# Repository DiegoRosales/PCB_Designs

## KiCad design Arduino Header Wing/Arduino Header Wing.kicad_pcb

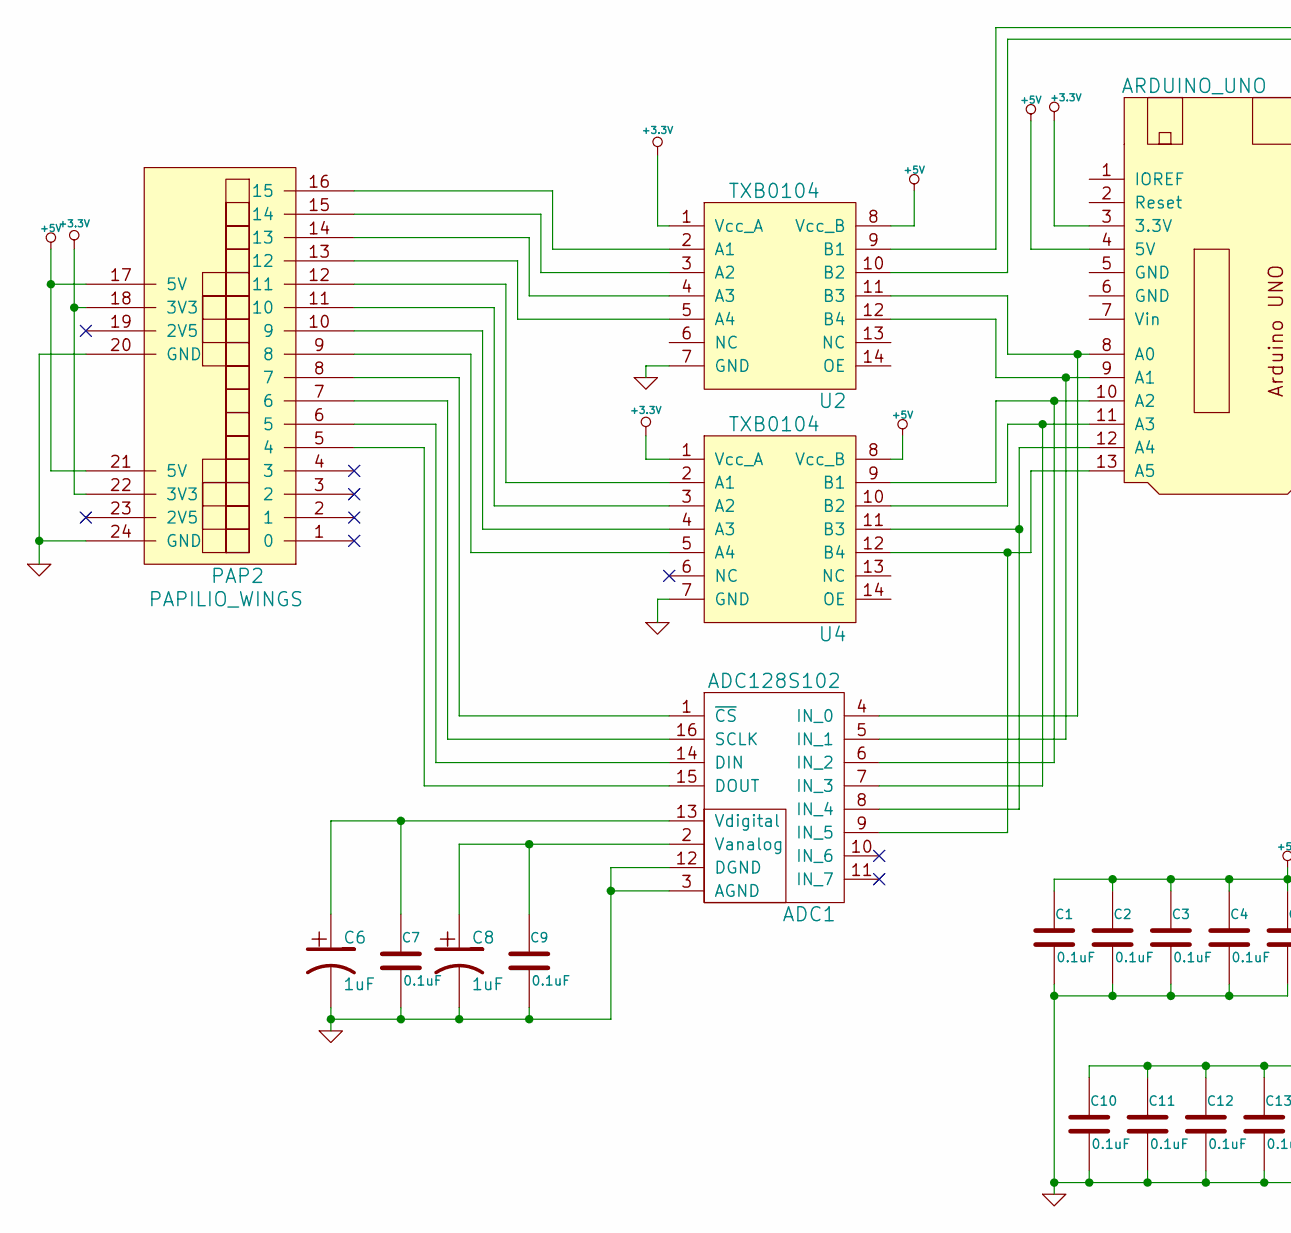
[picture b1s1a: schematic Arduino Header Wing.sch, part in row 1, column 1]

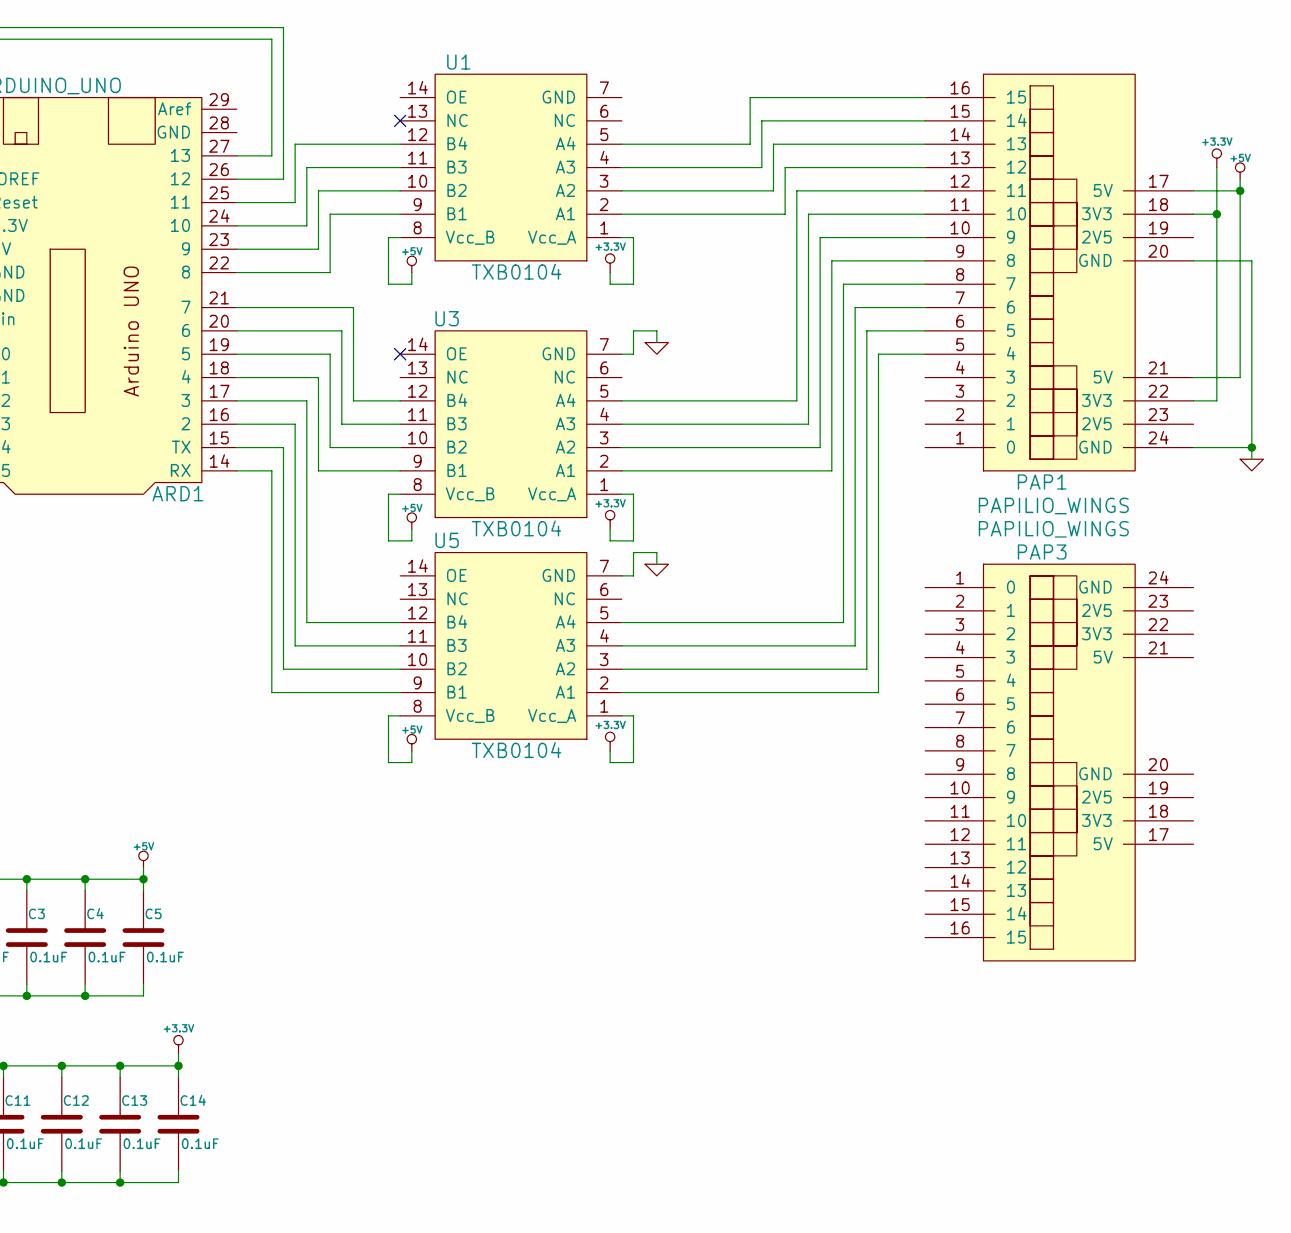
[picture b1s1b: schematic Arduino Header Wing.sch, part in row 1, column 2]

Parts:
ADC1: ADC128S102
ARD1: ARDUINO_UNO
C1, C2, C3, C4, C5, C7, C9, C10, C11, C12, C13, C14: 0.1uF
C6, C8: 1uF
PAP1, PAP2, PAP3: PAPILIO_WINGS
U1, U2, U3, U4, U5: TXB0104

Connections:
+3.3V: ARD1.3 (3.3V), C10.1, C11.1, C12.1, C13.1, C14.1, PAP1.18 (3V3), PAP1.22 (3V3), PAP2.18 (3V3), PAP2.22 (3V3), U1.1 (Vcc_A), U2.1 (Vcc_A), U3.1 (Vcc_A), U4.1 (Vcc_A), U5.1 (Vcc_A)
+5V: ARD1.4 (5V), C1.1, C2.1, C3.1, C4.1, C5.1, PAP1.17 (5V), PAP1.21 (5V), PAP2.17 (5V), PAP2.21 (5V), U1.8 (Vcc_B), U2.8 (Vcc_B), U3.8 (Vcc_B), U4.8 (Vcc_B), U5.8 (Vcc_B)
GND: ADC1.3 (AGND), ADC1.12 (DGND), C1.2, C2.2, C3.2, C4.2, C5.2, C6.2, C7.2, C8.2, C9.2, C10.2, C11.2, C12.2, C13.2, C14.2, PAP1.20 (GND), PAP1.24 (GND), PAP2.20 (GND), PAP2.24 (GND), U2.7 (GND), U3.7 (GND), U4.7 (GND), U5.7 (GND)
unnamed: ARD1.25 (11), U1.12 (B4)
unnamed: ARD1.24 (10), U1.11 (B3)
unnamed: ARD1.23 (9), U1.10 (B2)
unnamed: ARD1.22 (8), U1.9 (B1)
unnamed: PAP1.11 (10), U3.4 (A3)
unnamed: PAP1.14 (13), U1.3 (A2)
unnamed: PAP1.13 (12), U1.2 (A1)
unnamed: PAP1.12 (11), U3.5 (A4)
unnamed: PAP1.10 (9), U3.3 (A2)
unnamed: PAP1.9 (8), U3.2 (A1)
unnamed: PAP1.16 (15), U1.5 (A4)
unnamed: PAP1.15 (14), U1.4 (A3)
unnamed: PAP2.14 (13), U2.4 (A3)
unnamed: PAP2.16 (15), U2.2 (A1)
unnamed: PAP2.15 (14), U2.3 (A2)
unnamed: PAP2.13 (12), U2.5 (A4)
unnamed: PAP2.12 (11), U4.2 (A1)
unnamed: PAP2.11 (10), U4.3 (A2)
unnamed: ADC1.13 (Vdigital), C6.1, C7.1
unnamed: ARD1.26 (12), U2.9 (B1)
unnamed: PAP2.10 (9), U4.4 (A3)
unnamed: PAP2.9 (8), U4.5 (A4)
unnamed: PAP1.8 (7), U5.5 (A4)
unnamed: ADC1.14 (DIN), PAP2.6 (5)
unnamed: ADC1.15 (DOUT), PAP2.5 (4)
unnamed: PAP1.5 (4), U5.2 (A1)
unnamed: PAP1.7 (6), U5.4 (A3)
unnamed: PAP1.6 (5), U5.3 (A2)
unnamed: ADC1.1 (~CS), PAP2.8 (7)
unnamed: ADC1.16 (SCLK), PAP2.7 (6)
unnamed: ADC1.8 (IN_4), ARD1.12 (A4), U4.11 (B3)
unnamed: ADC1.4 (IN_0), ARD1.8 (A0), U2.11 (B3)
unnamed: ADC1.5 (IN_1), ARD1.9 (A1), U2.12 (B4)
unnamed: ADC1.6 (IN_2), ARD1.10 (A2), U4.9 (B1)
unnamed: ADC1.2 (Vanalog), C8.1, C9.1
unnamed: ARD1.15 (TX), U5.10 (B2)
unnamed: ARD1.16 (2), U5.11 (B3)
unnamed: ARD1.17 (3), U5.12 (B4)
unnamed: ARD1.18 (4), U3.9 (B1)
unnamed: ARD1.14 (RX), U5.9 (B1)
unnamed: ARD1.20 (6), U3.11 (B3)
unnamed: ARD1.21 (7), U3.12 (B4)
unnamed: ARD1.19 (5), U3.10 (B2)
unnamed: ADC1.7 (IN_3), ARD1.11 (A3), U4.10 (B2)
unnamed: ADC1.9 (IN_5), ARD1.13 (A5), U4.12 (B4)
unnamed: ARD1.27 (13), U2.10 (B2)

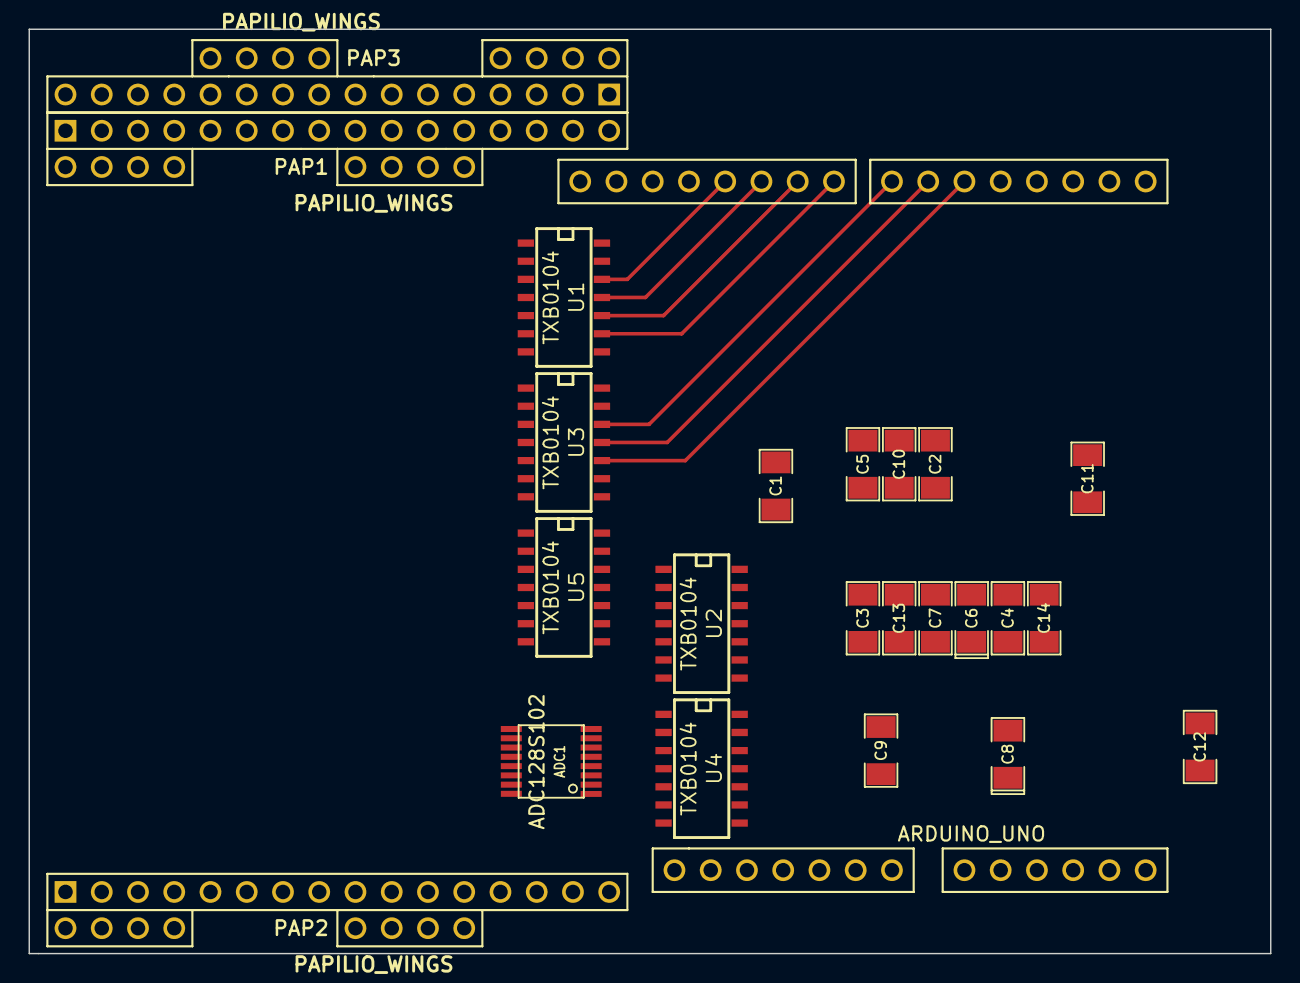
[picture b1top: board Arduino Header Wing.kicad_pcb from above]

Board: 2 copper layers, 87.0 x 64.8 mm, 24 parts (0 on the bottom side), 49 nets.

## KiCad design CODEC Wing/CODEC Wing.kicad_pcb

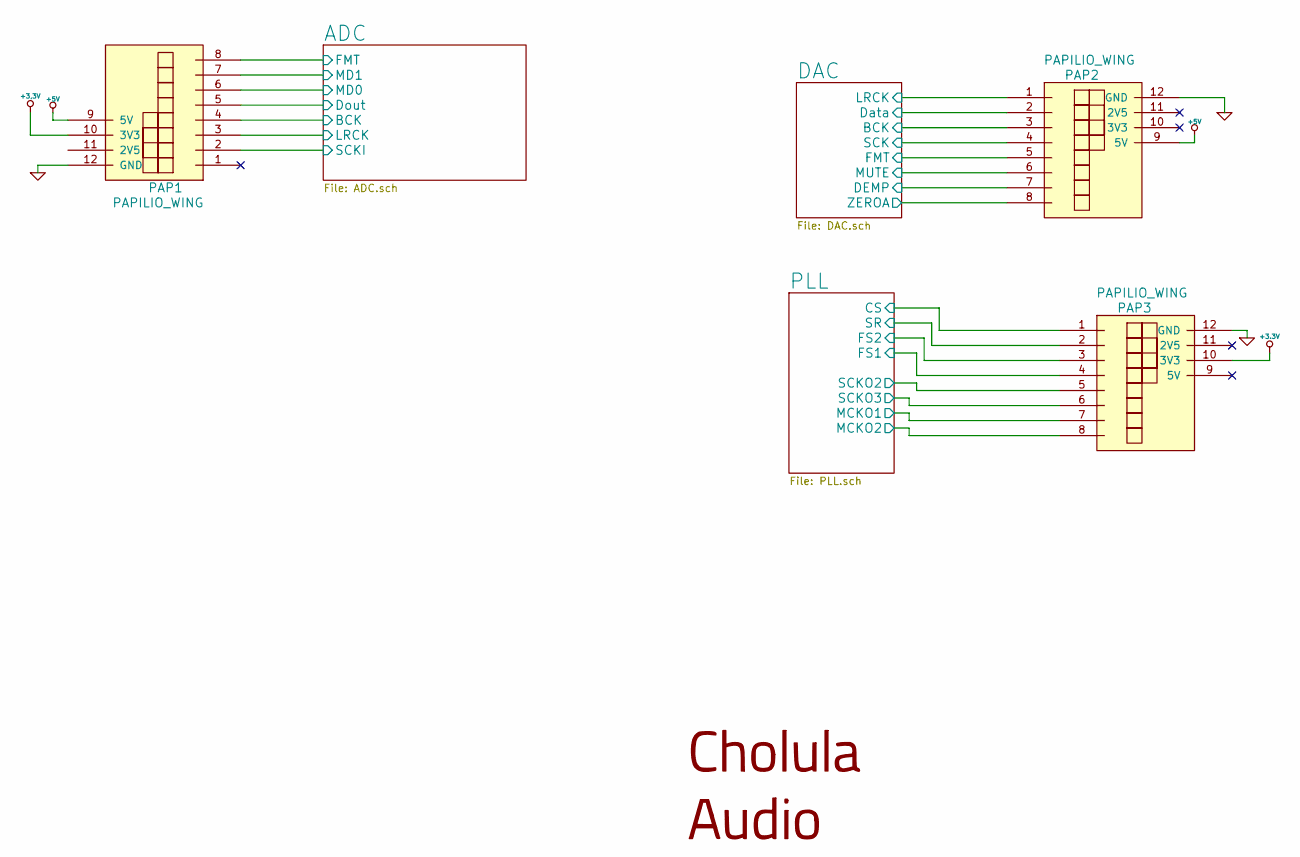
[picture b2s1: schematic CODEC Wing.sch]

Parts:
PAP1, PAP2, PAP3: PAPILIO_WING

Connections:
+5V: PAP1.9 (5V), PAP2.9 (5V); also elsewhere on the board
/ADC/BCK: PAP1.4; also elsewhere on the board
/ADC/Dout: PAP1.5; also elsewhere on the board
/ADC/FMT: PAP1.8; also elsewhere on the board
/ADC/LRCK: PAP1.3; also elsewhere on the board
/ADC/MD0: PAP1.6; also elsewhere on the board
/ADC/MD1: PAP1.7; also elsewhere on the board
/ADC/SCKI: PAP1.2; also elsewhere on the board
/DAC/BCK: PAP2.3; also elsewhere on the board
/DAC/DEMP: PAP2.7; also elsewhere on the board
/DAC/Data: PAP2.2; also elsewhere on the board
/DAC/FMT: PAP2.5; also elsewhere on the board
/DAC/LRCK: PAP2.1; also elsewhere on the board
/DAC/MUTE: PAP2.6; also elsewhere on the board
/DAC/SCK: PAP2.4; also elsewhere on the board
/DAC/ZEROA: PAP2.8; also elsewhere on the board
/PLL/CS: PAP3.1; also elsewhere on the board
/PLL/FS1: PAP3.4; also elsewhere on the board
/PLL/FS2: PAP3.3; also elsewhere on the board
/PLL/MCKO1: PAP3.7; also elsewhere on the board
/PLL/MCKO2: PAP3.8; also elsewhere on the board
/PLL/SCKO2: PAP3.5; also elsewhere on the board
/PLL/SCKO3: PAP3.6; also elsewhere on the board
/PLL/SR: PAP3.2; also elsewhere on the board
GND: PAP1.12 (GND), PAP2.12 (GND), PAP3.12 (GND); also elsewhere on the board

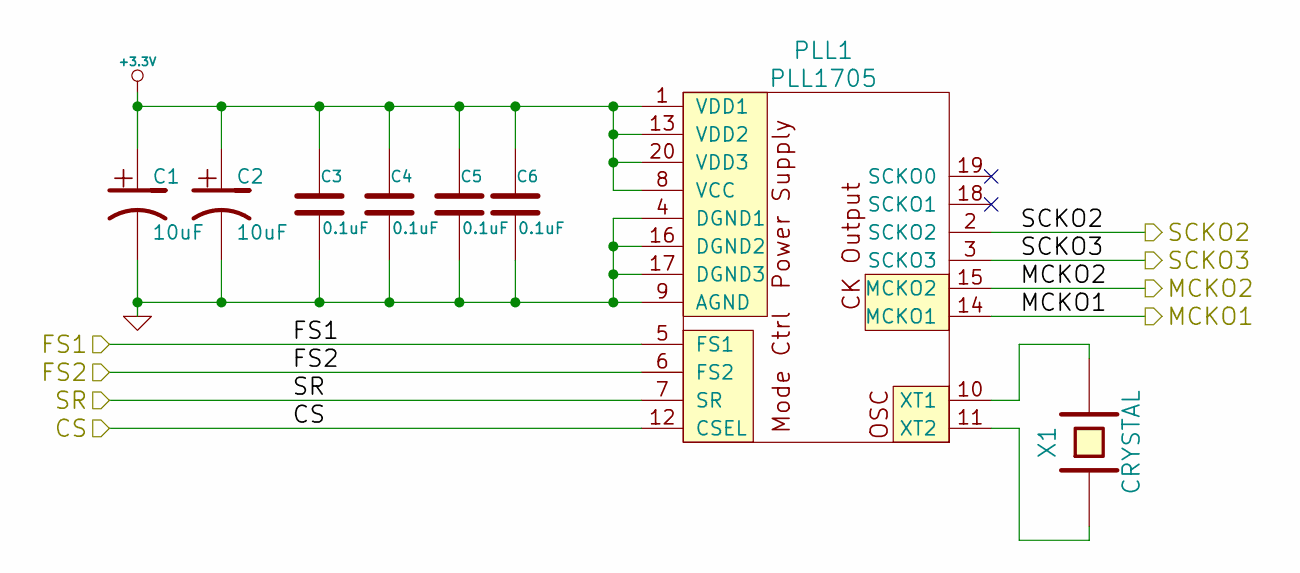
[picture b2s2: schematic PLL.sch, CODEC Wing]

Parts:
C1, C2: 10uF
C3, C4, C5, C6: 0.1uF
PLL1: PLL1705
X1: CRYSTAL

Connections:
/PLL/CS: PLL1.12 (CSEL); also elsewhere on the board
/PLL/FS1: PLL1.5 (FS1); also elsewhere on the board
/PLL/FS2: PLL1.6 (FS2); also elsewhere on the board
/PLL/MCKO1: PLL1.14 (MCKO1); also elsewhere on the board
/PLL/MCKO2: PLL1.15 (MCKO2); also elsewhere on the board
/PLL/SCKO2: PLL1.2 (SCKO2); also elsewhere on the board
/PLL/SCKO3: PLL1.3 (SCKO3); also elsewhere on the board
/PLL/SR: PLL1.7 (SR); also elsewhere on the board
GND: C1.2, C2.2, C3.2, C4.2, C5.2, C6.2, PLL1.4 (DGND1), PLL1.9 (AGND), PLL1.16 (DGND2), PLL1.17 (DGND3); also elsewhere on the board
unnamed: PLL1.10 (XT1), X1.2
unnamed: PLL1.11 (XT2), X1.1

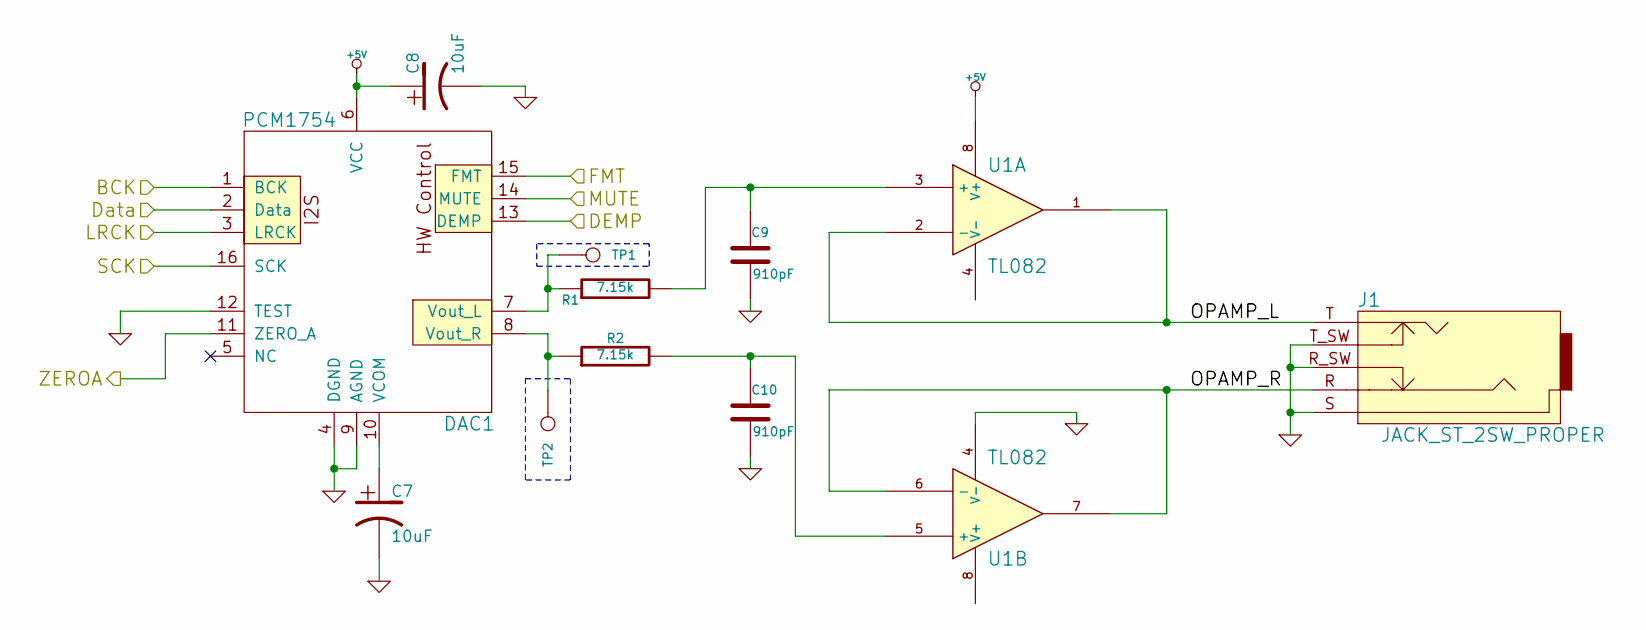
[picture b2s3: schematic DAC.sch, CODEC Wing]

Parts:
C7, C8: 10uF
C9, C10: 910pF
DAC1: PCM1754
J1: JACK_ST_2SW_PROPER
R1, R2: 7.15k
TP1, TP2: CONN_1
U1: TL082

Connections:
+5V: C8.1, DAC1.6 (VCC), U1.8 (V+); also elsewhere on the board
/DAC/BCK: DAC1.1 (BCK); also elsewhere on the board
/DAC/DEMP: DAC1.13 (DEMP); also elsewhere on the board
/DAC/Data: DAC1.2 (Data); also elsewhere on the board
/DAC/FMT: DAC1.15 (FMT); also elsewhere on the board
/DAC/LRCK: DAC1.3 (LRCK); also elsewhere on the board
/DAC/MUTE: DAC1.14 (MUTE); also elsewhere on the board
/DAC/OPAMP_L: J1.T, U1.1, U1.2 (-)
/DAC/OPAMP_R: J1.R, U1.6 (-), U1.7
/DAC/SCK: DAC1.16 (SCK); also elsewhere on the board
/DAC/ZEROA: DAC1.11 (ZERO_A); also elsewhere on the board
GND: C7.2, C8.2, C9.2, C10.2, DAC1.4 (DGND), DAC1.9 (AGND), DAC1.12 (TEST), J1.R_SW, J1.S, J1.T_SW, U1.4 (V-); also elsewhere on the board
unnamed: DAC1.7 (Vout_L), R1.1, TP1.1
unnamed: DAC1.8 (Vout_R), R2.1, TP2.1
unnamed: C9.1, R1.2, U1.3 (+)
unnamed: C10.1, R2.2, U1.5 (+)
unnamed: C7.1, DAC1.10 (VCOM)

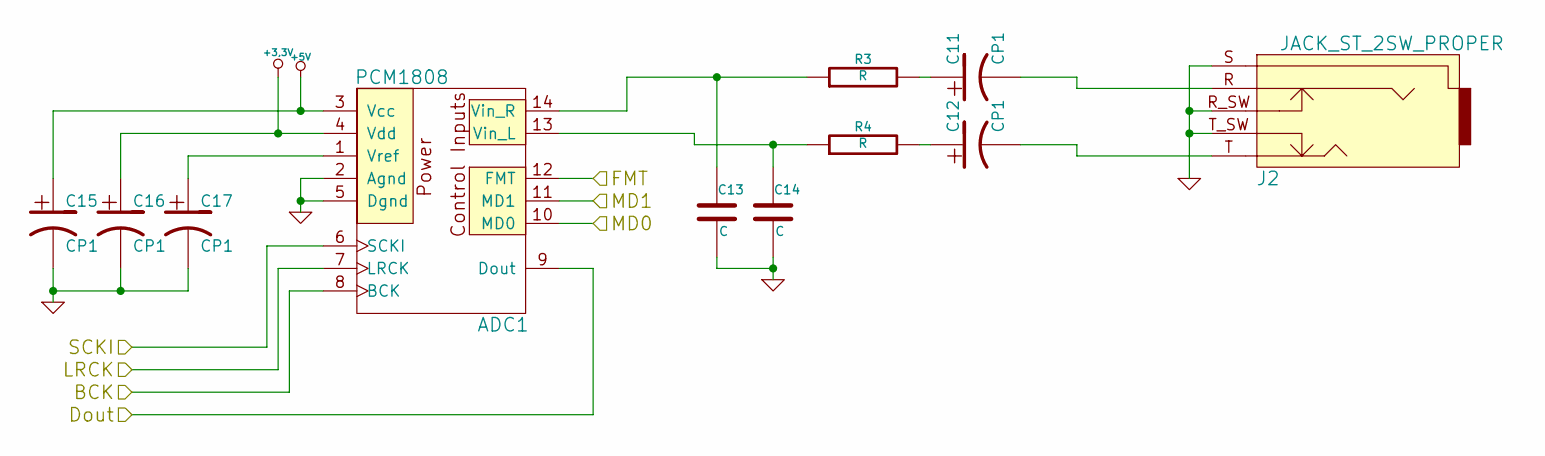
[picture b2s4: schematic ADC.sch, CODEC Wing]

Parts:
ADC1: PCM1808
C11, C12, C15, C16, C17: CP1
C13, C14: C
J2: JACK_ST_2SW_PROPER
R3, R4: R

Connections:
+5V: ADC1.3 (Vcc), C15.1; also elsewhere on the board
/ADC/BCK: ADC1.8 (BCK); also elsewhere on the board
/ADC/Dout: ADC1.9 (Dout); also elsewhere on the board
/ADC/FMT: ADC1.12 (FMT); also elsewhere on the board
/ADC/LRCK: ADC1.7 (LRCK); also elsewhere on the board
/ADC/MD0: ADC1.10 (MD0); also elsewhere on the board
/ADC/MD1: ADC1.11 (MD1); also elsewhere on the board
/ADC/SCKI: ADC1.6 (SCKI); also elsewhere on the board
GND: ADC1.2 (Agnd), ADC1.5 (Dgnd), C13.2, C14.2, C15.2, C16.2, C17.2, J2.R_SW, J2.S, J2.T_SW; also elsewhere on the board
unnamed: C12.2, J2.T
unnamed: C11.2, J2.R
unnamed: C12.1, R4.2
unnamed: C11.1, R3.2
unnamed 38: ADC1.14 (Vin_R), C13.1, R3.1; also elsewhere on the board
unnamed 39: ADC1.13 (Vin_L), C14.1, R4.1; also elsewhere on the board
unnamed: ADC1.1 (Vref), C17.1

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
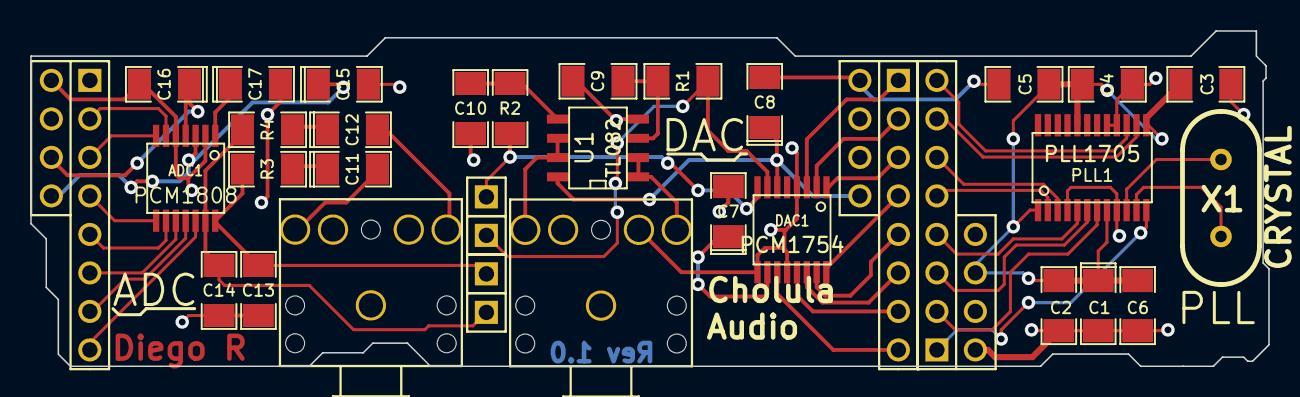
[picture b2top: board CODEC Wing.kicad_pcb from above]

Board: 2 copper layers, 81.7 x 22.1 mm, 35 parts (0 on the bottom side), 42 nets.

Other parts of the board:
TP3, TP4: CONN_1; PIN_ARRAY_1

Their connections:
unnamed 38: TP3.1; also elsewhere on the board
unnamed 39: TP4.1; also elsewhere on the board

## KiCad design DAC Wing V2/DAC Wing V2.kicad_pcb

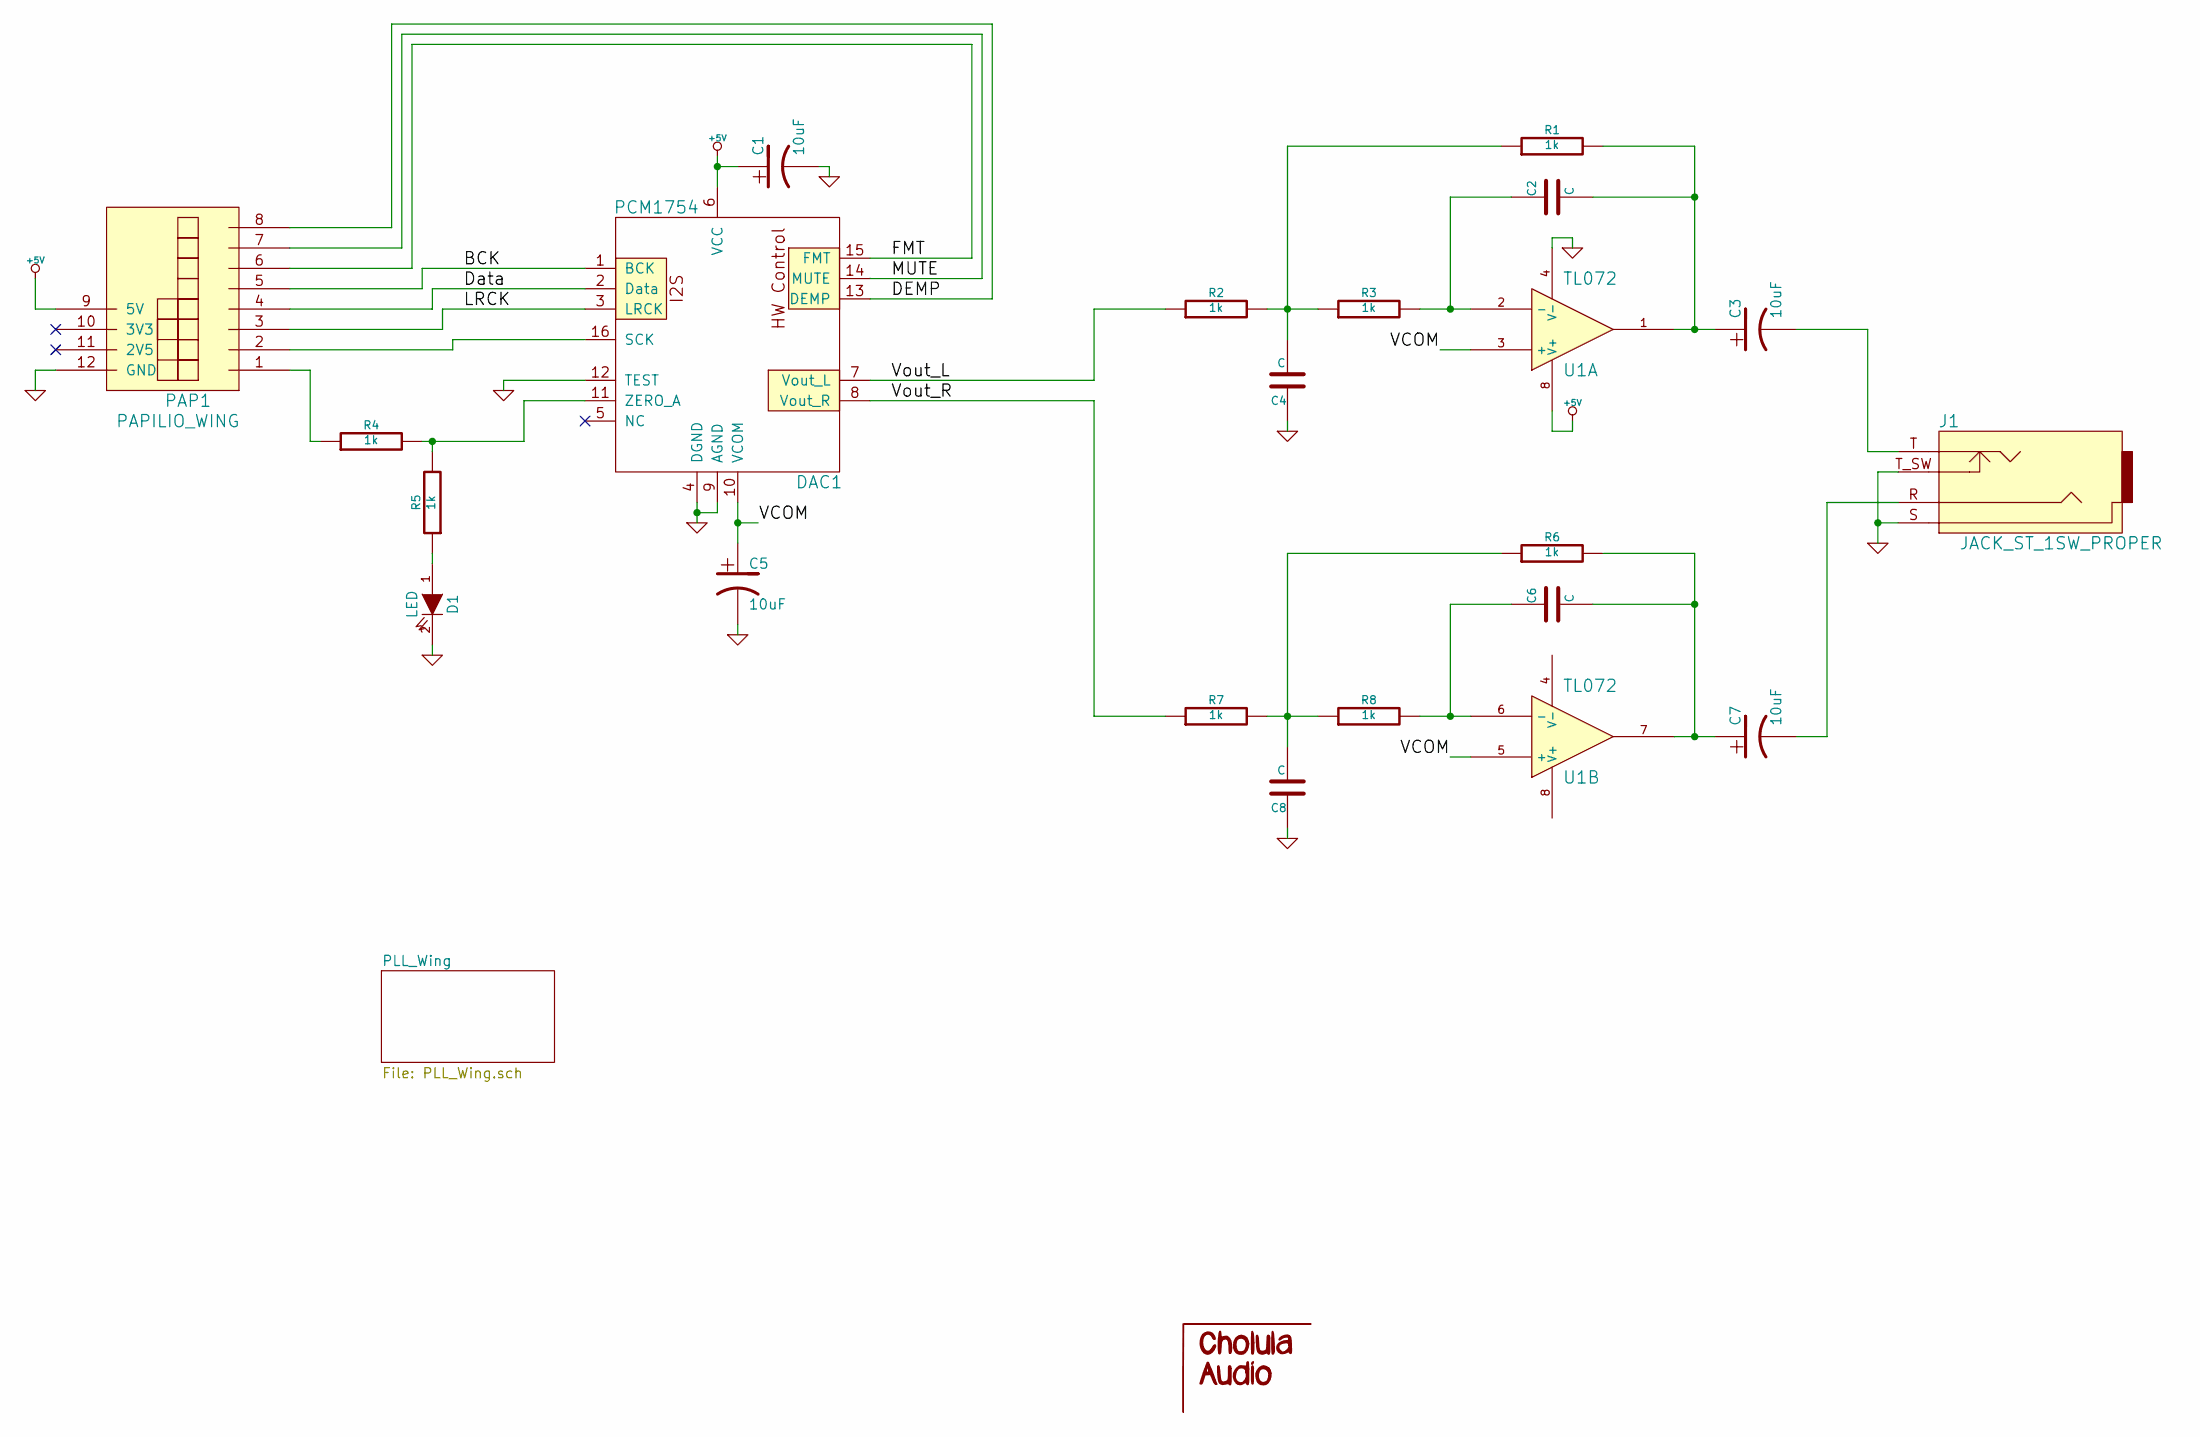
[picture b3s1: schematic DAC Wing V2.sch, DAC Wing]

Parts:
C1, C3, C5, C7: 10uF
C2, C4, C6, C8: C
D1: LED
DAC1: PCM1754
J1: JACK_ST_1SW_PROPER
PAP1: PAPILIO_WING
R1, R2, R3, R4, R5, R6, R7, R8: 1k
U1: TL072

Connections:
+5V: C1.1, DAC1.6 (VCC), PAP1.9 (5V), U1.8 (V+)
/BCK: DAC1.1 (BCK), PAP1.5
/DEMP: DAC1.13 (DEMP), PAP1.8
/Data: DAC1.2 (Data), PAP1.4
/FMT: DAC1.15 (FMT), PAP1.6
/LRCK: DAC1.3 (LRCK), PAP1.3
/MUTE: DAC1.14 (MUTE), PAP1.7
/VCOM: C5.1, DAC1.10 (VCOM), U1.3 (+), U1.5 (+)
/Vout_L: DAC1.7 (Vout_L), R2.1
/Vout_R: DAC1.8 (Vout_R), R7.1
GND: C1.2, C4.1, C5.2, C8.1, D1.2 (K), DAC1.4 (DGND), DAC1.9 (AGND), DAC1.12 (TEST), J1.S, J1.T_SW, PAP1.12 (GND), U1.4 (V-); also elsewhere on the board
unnamed: DAC1.11 (ZERO_A), R4.2, R5.2
unnamed: D1.1 (A), R5.1
unnamed: C8.2, R6.1, R7.2, R8.1
unnamed: C6.1, R8.2, U1.6 (-)
unnamed: C6.2, C7.1, R6.2, U1.7
unnamed: C4.2, R1.1, R2.2, R3.1
unnamed: C2.1, R3.2, U1.2 (-)
unnamed: DAC1.16 (SCK), PAP1.2
unnamed: PAP1.1, R4.1
unnamed: C2.2, C3.1, R1.2, U1.1
unnamed: C7.2, J1.R
unnamed: C3.2, J1.T

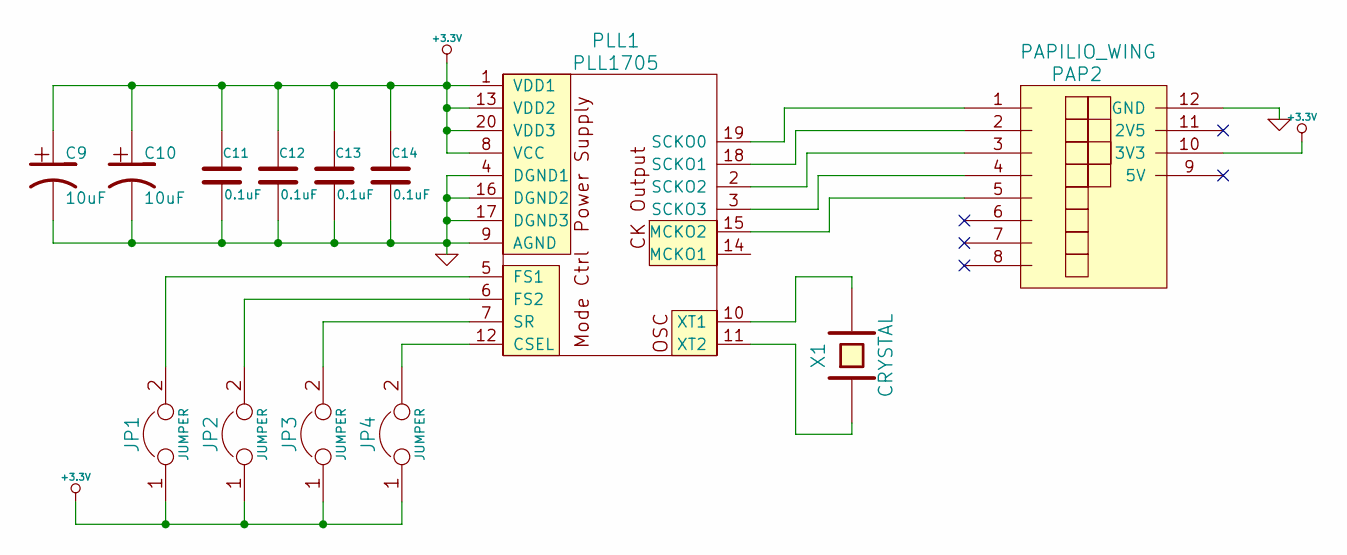
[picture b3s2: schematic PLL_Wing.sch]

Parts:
C9, C10: 10uF
C11, C12, C13, C14: 0.1uF
JP1, JP2, JP3, JP4: JUMPER
PAP2: PAPILIO_WING
PLL1: PLL1705
X1: CRYSTAL

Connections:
+3.3V: C9.1, C10.1, C11.1, C12.1, C13.1, C14.1, JP1.1, JP2.1, JP3.1, JP4.1, PAP2.10 (3V3), PLL1.1 (VDD1), PLL1.8 (VCC), PLL1.13 (VDD2), PLL1.20 (VDD3)
GND: C9.2, C10.2, C11.2, C12.2, C13.2, C14.2, PAP2.12 (GND), PLL1.4 (DGND1), PLL1.9 (AGND), PLL1.16 (DGND2), PLL1.17 (DGND3); also elsewhere on the board
unnamed: JP3.2, PLL1.7 (SR)
unnamed: JP2.2, PLL1.6 (FS2)
unnamed: JP4.2, PLL1.12 (CSEL)
unnamed: PAP2.4, PLL1.3 (SCKO3)
unnamed: JP1.2, PLL1.5 (FS1)
unnamed: PAP2.1, PLL1.19 (SCKO0)
unnamed: PAP2.2, PLL1.18 (SCKO1)
unnamed: PAP2.3, PLL1.2 (SCKO2)
unnamed: PLL1.11 (XT2), X1.1
unnamed: PAP2.5, PLL1.15 (MCKO2)
unnamed: PLL1.10 (XT1), X1.2

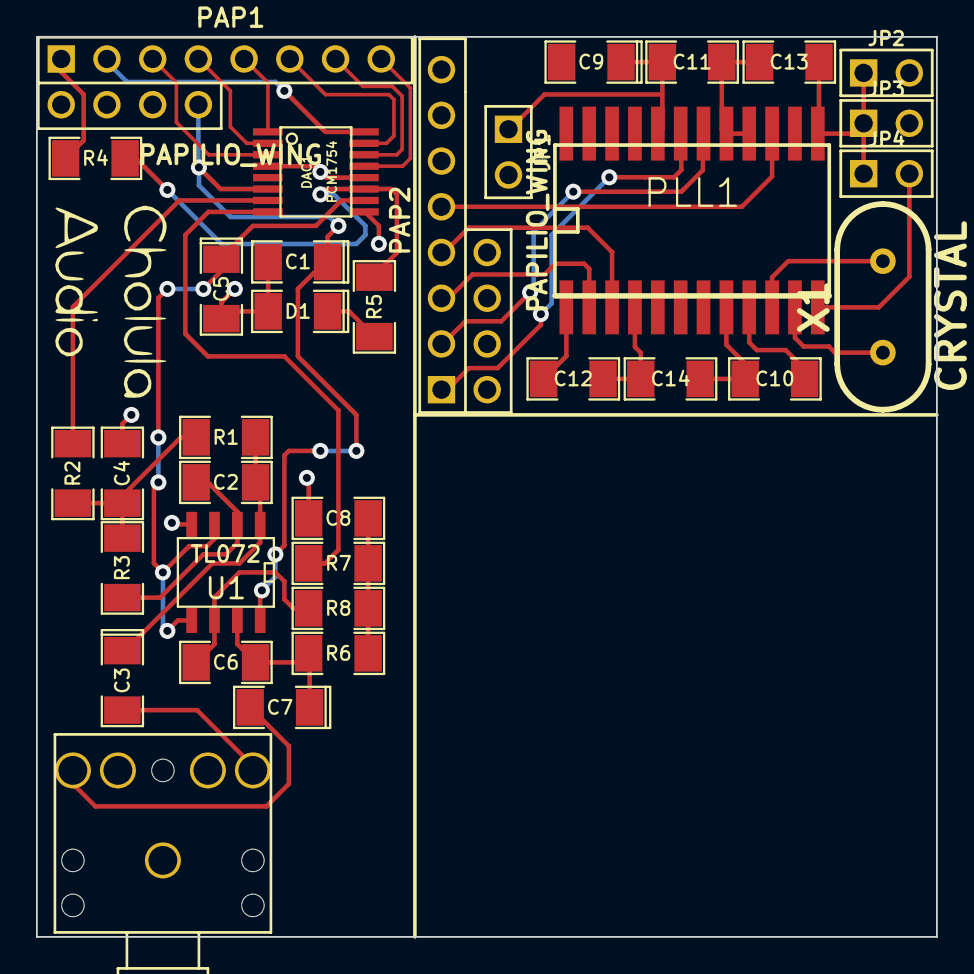
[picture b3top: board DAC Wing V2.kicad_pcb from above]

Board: 2 copper layers, 50.0 x 50.0 mm, 34 parts (0 on the bottom side), 35 nets.

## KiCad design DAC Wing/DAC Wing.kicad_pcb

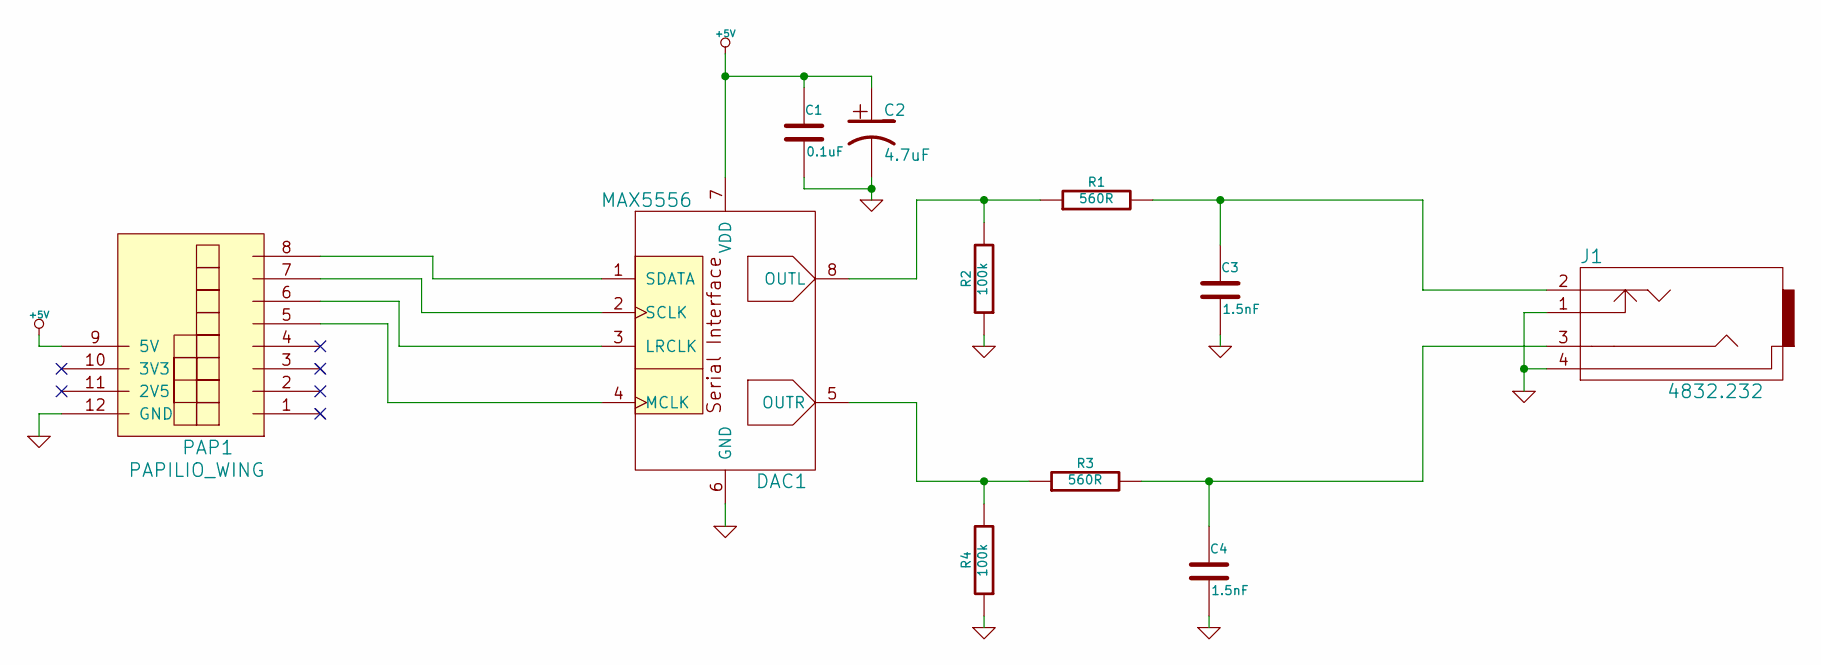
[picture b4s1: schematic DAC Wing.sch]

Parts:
C1: 0.1uF
C2: 4.7uF
C3, C4: 1.5nF
DAC1: MAX5556
J1: 4832.232
PAP1: PAPILIO_WING
R1, R3: 560R
R2, R4: 100k

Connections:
+5V: C1.1, C2.1, DAC1.7 (VDD), PAP1.9 (5V)
GND: C1.2, C2.2, C3.2, C4.2, DAC1.6 (GND), J1.1, J1.4, PAP1.12 (GND), R2.1, R4.1
unnamed: DAC1.5 (OUTR), R3.1, R4.2
unnamed: DAC1.8 (OUTL), R1.1, R2.2
unnamed: C4.1, J1.3, R3.2
unnamed: DAC1.4 (MCLK), PAP1.5
unnamed: DAC1.3 (LRCLK), PAP1.6
unnamed: DAC1.2 (SCLK), PAP1.7
unnamed: DAC1.1 (SDATA), PAP1.8
unnamed: C3.1, J1.2, R1.2

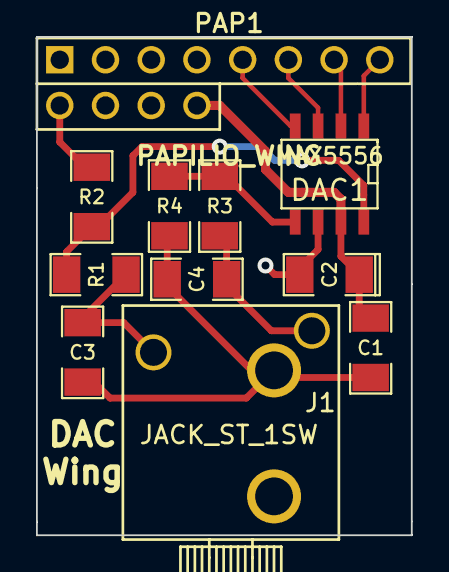
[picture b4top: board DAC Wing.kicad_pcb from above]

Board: 2 copper layers, 20.8 x 27.7 mm, 11 parts (0 on the bottom side), 10 nets.
